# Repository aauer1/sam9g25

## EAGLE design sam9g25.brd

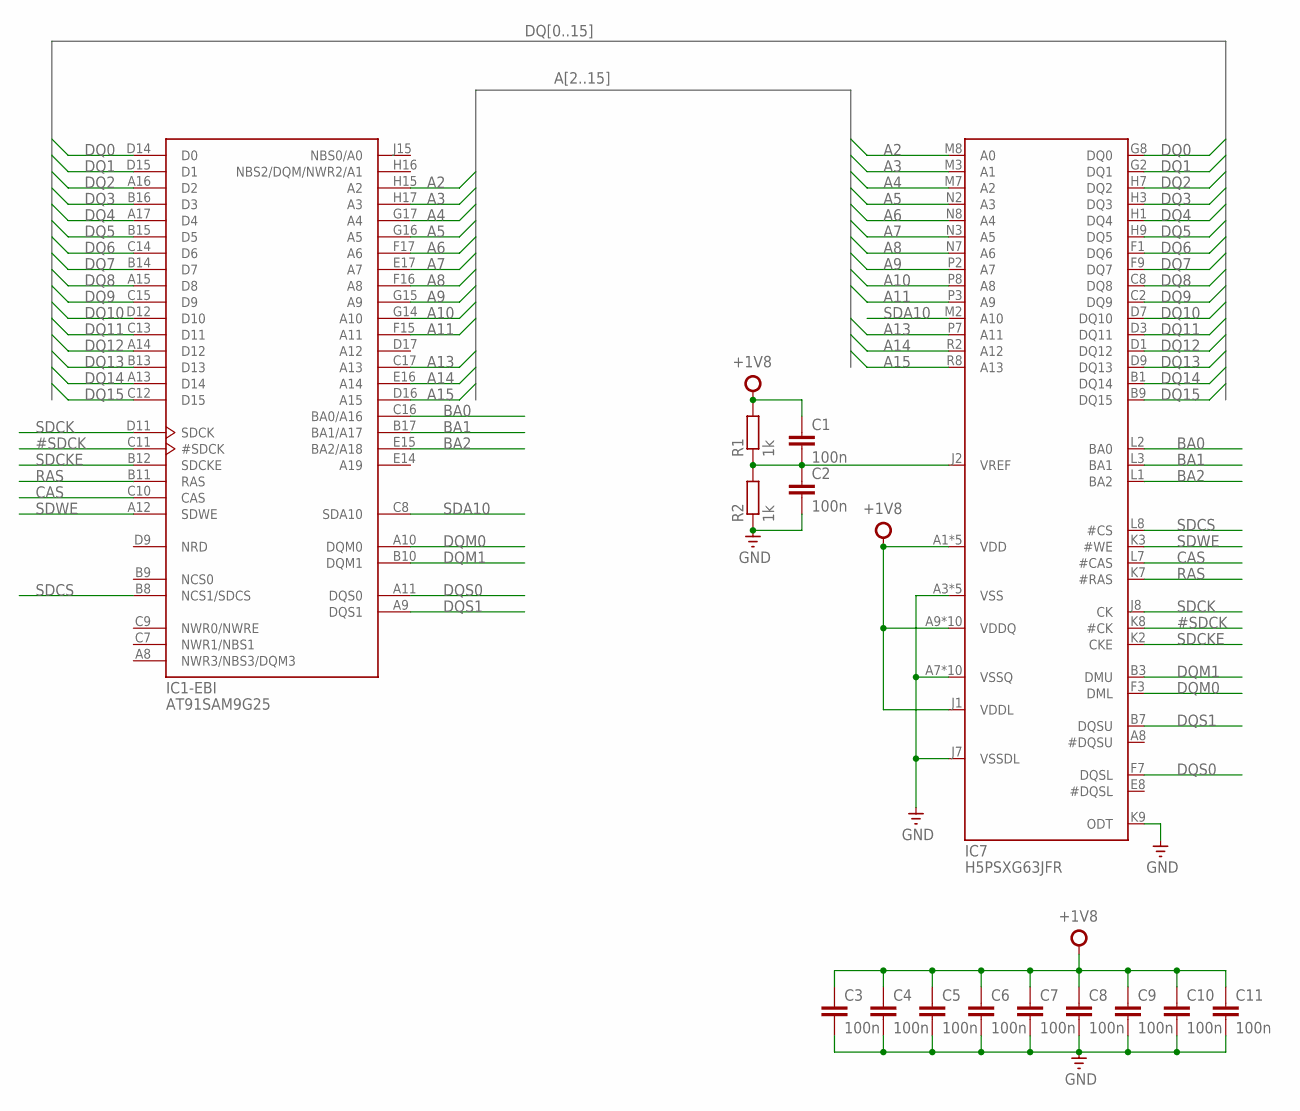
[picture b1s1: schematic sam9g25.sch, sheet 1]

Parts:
C1, C2, C3, C4, C5, C6, C7, C8, C9, C10, C11: 100n; C0603; MPN MC0603B104K250CT
IC1: AT91SAM9G25; LFBGA217; MPN AT91SAM9G25-CU
IC7: H5PSXG63JFR; FBGA84; MPN H5PS1G63JFR-S5C
R1, R2: 1k; R0603; MPN MC0063W060351K5

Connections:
#SDCK: IC1.C11 (#SDCK), IC7.K8 (#CK)
+1V8: C1.1, C3.1, C4.1, C5.1, C6.1, C7.1, C8.1, C9.1, C10.1, C11.1, IC7.A1 (VDD), IC7.A9 (VDDQ), IC7.C1 (VDDQ), IC7.C3 (VDDQ), IC7.C7 (VDDQ), IC7.C9 (VDDQ), IC7.E1 (VDD), IC7.E9 (VDDQ), IC7.G1 (VDDQ), IC7.G3 (VDDQ), IC7.G7 (VDDQ), IC7.G9 (VDDQ), IC7.J1 (VDDL), IC7.J9 (VDD), IC7.M9 (VDD), IC7.R1 (VDD), R1.2; also elsewhere on the board
A2: IC1.H15 (A2), IC7.M8 (A0)
A3: IC1.H17 (A3), IC7.M3 (A1)
A4: IC1.G17 (A4), IC7.M7 (A2)
A5: IC1.G16 (A5), IC7.N2 (A3)
A6: IC1.F17 (A6), IC7.N8 (A4)
A7: IC1.E17 (A7), IC7.N3 (A5)
A8: IC1.F16 (A8), IC7.N7 (A6)
A9: IC1.G15 (A9), IC7.P2 (A7)
A10: IC1.G14 (A10), IC7.P8 (A8)
A11: IC1.F15 (A11), IC7.P3 (A9)
A13: IC1.C17 (A13), IC7.P7 (A11)
A14: IC1.E16 (A14), IC7.R2 (A12)
A15: IC1.D16 (A15), IC7.R8 (A13)
BA0: IC1.C16 (BA0/A16), IC7.L2 (BA0)
BA1: IC1.B17 (BA1/A17), IC7.L3 (BA1)
BA2: IC1.E15 (BA2/A18), IC7.L1 (BA2)
CAS: IC1.C10 (CAS), IC7.L7 (#CAS)
DQ0: IC1.D14 (D0), IC7.G8 (DQ0)
DQ1: IC1.D15 (D1), IC7.G2 (DQ1)
DQ2: IC1.A16 (D2), IC7.H7 (DQ2)
DQ3: IC1.B16 (D3), IC7.H3 (DQ3)
DQ4: IC1.A17 (D4), IC7.H1 (DQ4)
DQ5: IC1.B15 (D5), IC7.H9 (DQ5)
DQ6: IC1.C14 (D6), IC7.F1 (DQ6)
DQ7: IC1.B14 (D7), IC7.F9 (DQ7)
DQ8: IC1.A15 (D8), IC7.C8 (DQ8)
DQ9: IC1.C15 (D9), IC7.C2 (DQ9)
DQ10: IC1.D12 (D10), IC7.D7 (DQ10)
DQ11: IC1.C13 (D11), IC7.D3 (DQ11)
DQ12: IC1.A14 (D12), IC7.D1 (DQ12)
DQ13: IC1.B13 (D13), IC7.D9 (DQ13)
DQ14: IC1.A13 (D14), IC7.B1 (DQ14)
DQ15: IC1.C12 (D15), IC7.B9 (DQ15)
DQM0: IC1.A10 (DQM0), IC7.F3 (DML)
DQM1: IC1.B10 (DQM1), IC7.B3 (DMU)
DQS0: IC1.A11 (DQS0), IC7.F7 (DQSL)
DQS1: IC1.A9 (DQS1), IC7.B7 (DQSU)
GND: C2.2, C3.2, C4.2, C5.2, C6.2, C7.2, C8.2, C9.2, C10.2, C11.2, IC7.A3 (VSS), IC7.A7 (VSSQ), IC7.B2 (VSSQ), IC7.B8 (VSSQ), IC7.D2 (VSSQ), IC7.D8 (VSSQ), IC7.E3 (VSS), IC7.E7 (VSSQ), IC7.F2 (VSSQ), IC7.F8 (VSSQ), IC7.H2 (VSSQ), IC7.H8 (VSSQ), IC7.J3 (VSS), IC7.J7 (VSSDL), IC7.K9 (ODT), IC7.N1 (VSS), IC7.P9 (VSS), R2.1; also elsewhere on the board
unnamed: C1.2, C2.1, IC7.J2 (VREF), R1.1, R2.2
RAS: IC1.B11 (RAS), IC7.K7 (#RAS)
SDA10: IC1.C8 (SDA10), IC7.M2 (A10)
SDCK: IC1.D11 (SDCK), IC7.J8 (CK)
SDCKE: IC1.B12 (SDCKE), IC7.K2 (CKE)
SDCS: IC1.B8 (NCS1/SDCS), IC7.L8 (#CS)
SDWE: IC1.A12 (SDWE), IC7.K3 (#WE)

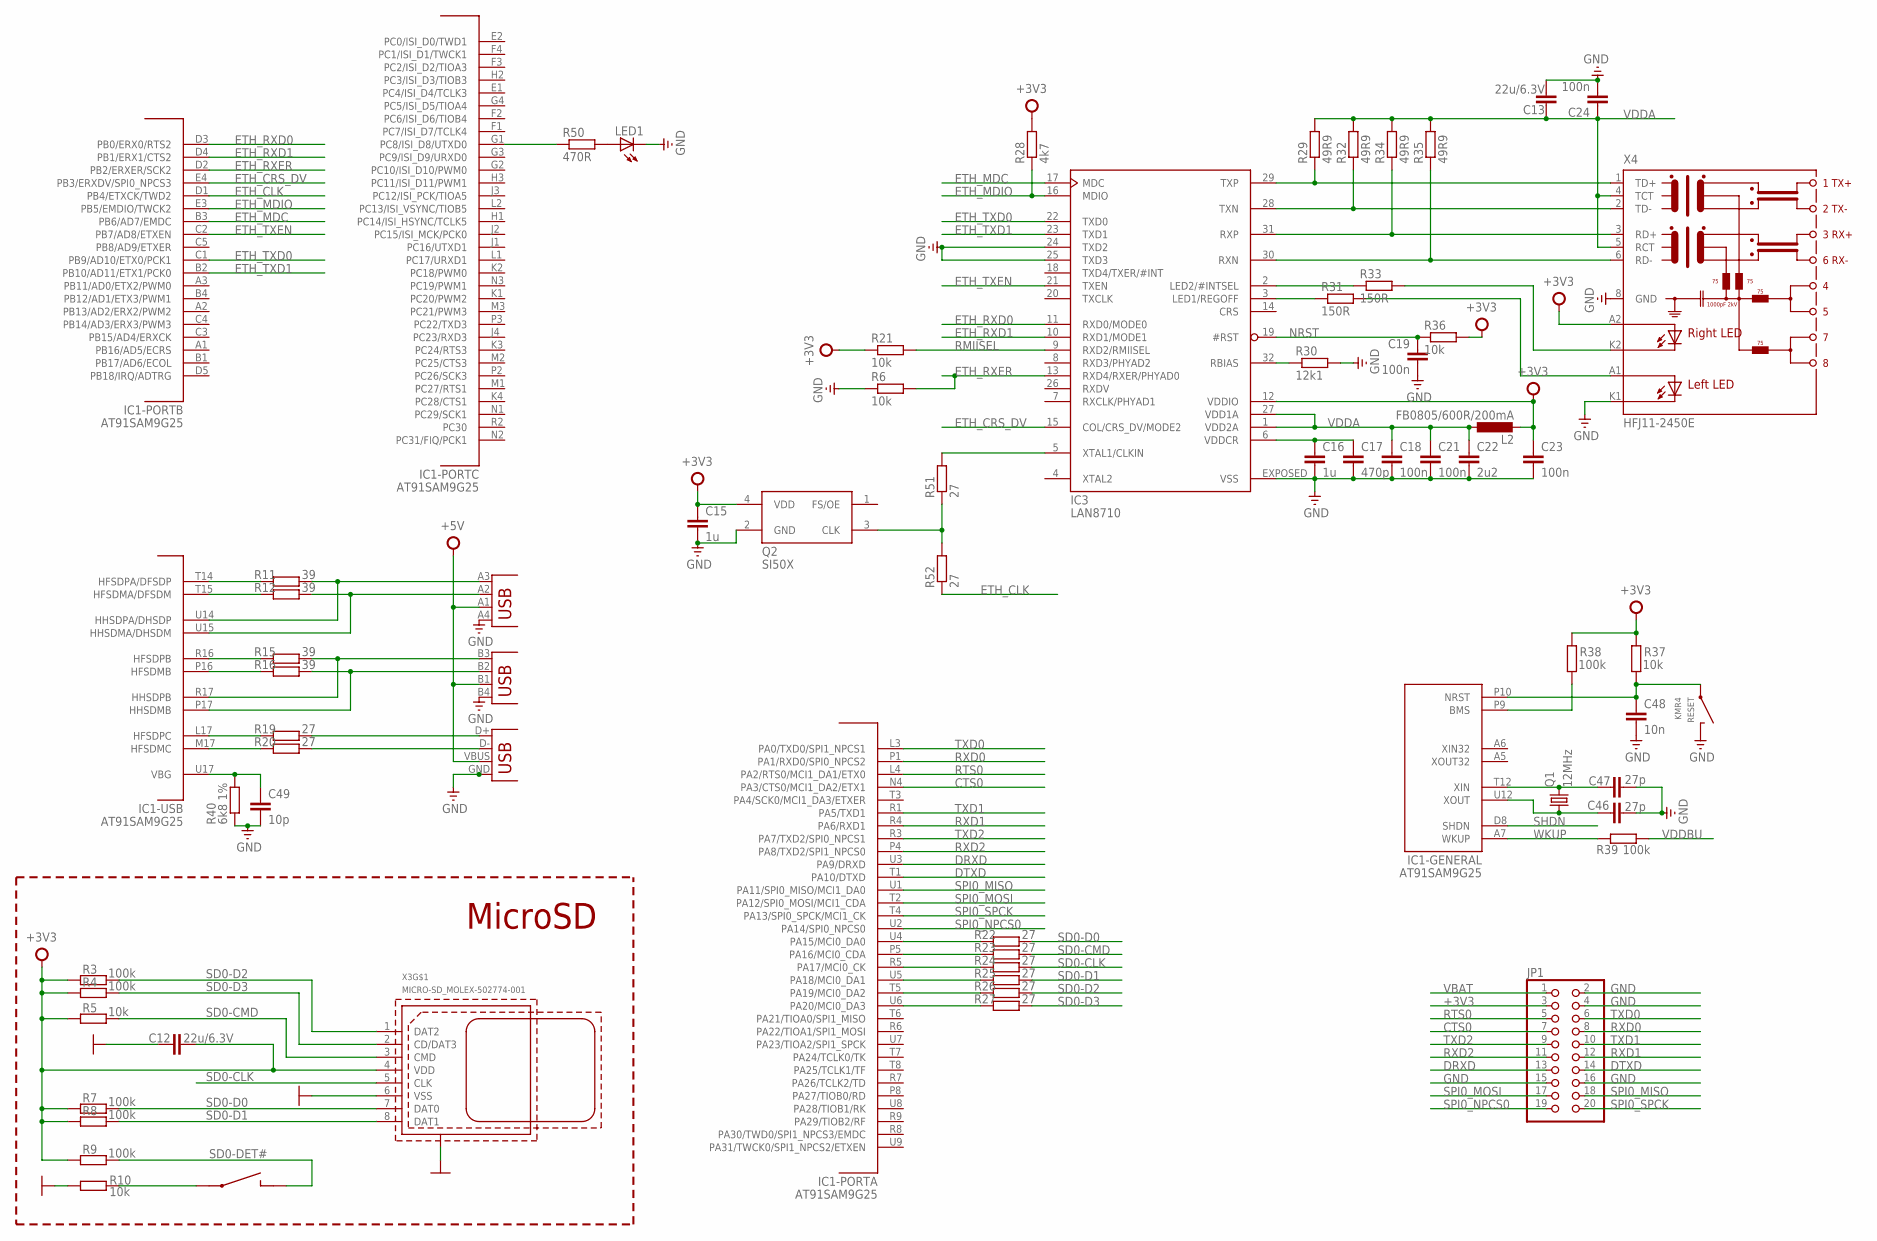
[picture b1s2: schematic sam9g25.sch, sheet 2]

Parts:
C12, C13: 22u/6.3V; C0805; MPN C2012X5R0J226M/1.25
C15: 1u; C0603; MPN MC0603N270J500CT
C16: 1u; C0603; MPN MC0603X105K100CT
C17: 470p; C0603; MPN MC0603B471K500CT
C18, C19, C21, C23, C24: 100n; C0603; MPN MC0603B104K250CT
C22: 2u2; C0603; MPN MC0603X225K6R3CT
C46, C47: 27p; C0603; MPN MC0603N270J500CT
C48: 10n; C0603; MPN MC0603B103K160CT
C49: 10p; C0603; MPN MC0603N100J500CT
IC1: AT91SAM9G25; LFBGA217; MPN AT91SAM9G25-CU
IC3: LAN8710; QFN32; MPN LAN8710A-EZK
JP1: PINHD-2X10; 2X10
L2: FB0805/600R/200mA; L2012C; MPN BLM21BD601SN1D
LED1: LEDCHIP-LED0603; CHIP-LED0603; MPN KP-1608SURCK
Q1: 12MHz; SMD5032; MPN 7A-12.000MAAJ-T
Q2: SI50X; DFN4
R3, R4, R7, R8, R9, R38, R39: 100k; R0603; MPN MC0063W06035100K
R5, R6, R10, R21, R37: 10k; R0603; MPN RC0603FR-0710KL
R11, R12, R15, R16: 39; R0603; MPN CRCW060339R0FKEA
R19, R20, R22, R23, R24, R25, R26, R27: 27; R0603; MPN MC0063W0603527R
R28: 4k7; R0603; MPN MC0063W060354K7
R29, R32, R34, R35: 49R9; R0603; MPN ERJ3GEYJ510V
R30: 12k1; R0603; MPN ERJ3EKF1212V
R31, R33: 150R; R0603; MPN MC0063W06035150R
R36: 10k; R0603; MPN ERJ3EKF1212V
R40: 6k8 1%; R0603; MPN MCMR06X6801FTL
R50: 470R; R0603; MPN MCMR06X1001FTL
R51, R52: 27; R0603; MPN RC0603FR-0710KL
RESET: KMR4; MPN KMR421NGULCLFS
X1: USB-DOUBLE; USB-DOUBLE-FCI; MPN 72309-8034BLF
X3: MICRO-SD_MOLEX-502774-001; MOLEX-MICRO-SD; MPN 502774-0891
X4: HFJ11-2450E; HFJ11_LED
X5: USB-A-HU

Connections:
+3V3: C12.2, C15.1, C23.1, IC3.12 (VDDIO), JP1.3, L2.2, Q2.4 (VDD), R3.2, R4.2, R5.2, R7.2, R8.2, R9.2, R21.1, R28.2, R36.2, R37.2, R38.2, X3.4 (VDD), X4.A2 (A-R); also elsewhere on the board
+5V: X1.A1 (VBUS), X1.B1 (VBUS), X5.VBUS; also elsewhere on the board
CTS0: IC1.N4 (PA3/CTS0/MCI1_DA2/ETX1), JP1.7
DRXD: IC1.U3 (PA9/DRXD), JP1.13
DTXD: IC1.T1 (PA10/DTXD), JP1.14
ETH_CLK: IC1.D1 (PB4/ETXCK/TWD2), R52.1
ETH_CRS_DV: IC1.E4 (PB3/ERXDV/SPI0_NPCS3), IC3.15 (COL/CRS_DV/MODE2)
ETH_MDC: IC1.B3 (PB6/AD7/EMDC), IC3.17 (MDC)
ETH_MDIO: IC1.E3 (PB5/EMDIO/TWCK2), IC3.16 (MDIO), R28.1
ETH_RXD0: IC1.D3 (PB0/ERX0/RTS2), IC3.11 (RXD0/MODE0)
ETH_RXD1: IC1.D4 (PB1/ERX1/CTS2), IC3.10 (RXD1/MODE1)
ETH_RXER: IC1.D2 (PB2/ERXER/SCK2), IC3.13 (RXD4/RXER/PHYAD0), R6.2
ETH_TXD0: IC1.C1 (PB9/AD10/ETX0/PCK1), IC3.22 (TXD0)
ETH_TXD1: IC1.B2 (PB10/AD11/ETX1/PCK0), IC3.23 (TXD1)
ETH_TXEN: IC1.C2 (PB7/AD8/ETXEN), IC3.21 (TXEN)
GND: C12.1, C13.2, C15.2, C16.2, C17.2, C18.2, C19.2, C21.2, C22.2, C23.2, C24.2, C46.2, C47.2, C48.2, C49.2, IC3.24 (TXD2), IC3.25 (TXD3), IC3.EXPOSED (VSS), JP1.2, JP1.4, JP1.15, JP1.16, LED1.C, Q2.2 (GND), R6.1, R10.2, R30.2, R40.1, RESET.2, RESET.4, X1.A4 (GND), X1.B4 (GND), X3.6 (VSS), X3.SHIELD@1, X3.SHIELD@2, X3.SHIELD@3, X3.SHIELD@4, X4.8 (GND), X4.K1 (C-L), X5.GND; also elsewhere on the board
HFSDMA: IC1.T15 (HFSDMA/DFSDM), R12.1
HFSDMB: IC1.P16 (HFSDMB), R16.1
HFSDMC: IC1.M17 (HFSDMC), R20.1
HFSDPA: IC1.T14 (HFSDPA/DFSDP), R11.1
HFSDPB: IC1.R16 (HFSDPB), R15.1
HFSDPC: IC1.L17 (HFSDPC), R19.1
HHSDMA: IC1.U15 (HHSDMA/DHSDM), R12.2, X1.A2 (D-)
HHSDMB: IC1.P17 (HHSDMB), R16.2, X1.B2 (D-)
HHSDPA: IC1.U14 (HHSDPA/DHSDP), R11.2, X1.A3 (D+)
HHSDPB: IC1.R17 (HHSDPB), R15.2, X1.B3 (D+)
unnamed: IC3.5 (XTAL1/CLKIN), R51.2
unnamed: R19.2, X5.D+
unnamed: R20.2, X5.D-
unnamed: IC1.U6 (PA20/MCI0_DA3), R27.1
unnamed: IC1.T5 (PA19/MCI0_DA2), R26.1
unnamed: IC1.U5 (PA18/MCI0_DA1), R25.1
unnamed: IC1.R5 (PA17/MCI0_CK), R24.1
unnamed: IC1.P5 (PA16/MCI0_CDA), R23.1
unnamed: IC1.U4 (PA15/MCI0_DA0), R22.1
unnamed: C49.1, IC1.U17 (VBG), R40.2
unnamed: C46.1, IC1.U12 (XOUT), Q1.1
unnamed: C47.1, IC1.T12 (XIN), Q1.2
unnamed: IC1.P9 (BMS), R38.1
unnamed: IC3.32 (RBIAS), R30.1
unnamed: C16.1, C17.1, IC3.6 (VDDCR)
unnamed: IC1.G1 (PC8/ISI_D8/UTXD0), R50.1
unnamed: LED1.A, R50.2
unnamed: Q2.3 (CLK), R51.1, R52.2
unnamed: R10.1, X3.SW1
unnamed: IC3.2 (LED2/#INTSEL), R33.1
unnamed: IC3.3 (LED1/REGOFF), R31.1
unnamed: IC3.30 (RXN), R35.1, X4.6 (RD-)
unnamed: IC3.31 (RXP), R34.1, X4.3 (RD+)
unnamed: IC3.29 (TXP), R29.1, X4.1 (TD+)
unnamed: R33.2, X4.K2 (C-R)
unnamed: R31.2, X4.A1 (A-L)
unnamed: IC3.28 (TXN), R32.1, X4.2 (TD-)
NRST: C19.1, C48.1, IC1.P10 (NRST), IC3.19 (#RST), R36.1, R37.1, RESET.1, RESET.3
RMIISEL: IC3.9 (RXD2/RMIISEL), R21.2
RTS0: IC1.L4 (PA2/RTS0/MCI1_DA1/ETX0), JP1.5
RXD0: IC1.P1 (PA1/RXD0/SPI0_NPCS2), JP1.8
RXD1: IC1.R4 (PA6/RXD1), JP1.12
RXD2: IC1.P4 (PA8/TXD2/SPI1_NPCS0), JP1.11
SD0-CLK: R24.2, X3.5 (CLK)
SD0-CMD: R5.1, R23.2, X3.3 (CMD)
SD0-D0: R7.1, R22.2, X3.7 (DAT0)
SD0-D1: R8.1, R25.2, X3.8 (DAT1)
SD0-D2: R3.1, R26.2, X3.1 (DAT2)
SD0-D3: R4.1, R27.2, X3.2 (CD/DAT3)
SD0-DET#: R9.1, X3.SW2
SHDN: IC1.D8 (SHDN)
SPI0_MISO: IC1.U1 (PA11/SPI0_MISO/MCI1_DA0), JP1.18
SPI0_MOSI: IC1.T2 (PA12/SPI0_MOSI/MCI1_CDA), JP1.17
SPI0_NPCS0: IC1.U2 (PA14/SPI0_NPCS0), JP1.19
SPI0_SPCK: IC1.T4 (PA13/SPI0_SPCK/MCI1_CK), JP1.20
TXD0: IC1.L3 (PA0/TXD0/SPI1_NPCS1), JP1.6
TXD1: IC1.R1 (PA5/TXD1), JP1.10
TXD2: IC1.R3 (PA7/TXD2/SPI0_NPCS1), JP1.9
VBAT: JP1.1; also elsewhere on the board
VDDA: C13.1, C18.1, C21.1, C22.1, C24.1, IC3.1 (VDD2A), IC3.27 (VDD1A), L2.1, R29.2, R32.2, R34.2, R35.2, X4.4 (TCT), X4.5 (RCT)
VDDBU: R39.1; also elsewhere on the board
WKUP: IC1.A7 (WKUP), R39.2

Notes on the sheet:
MicroSD

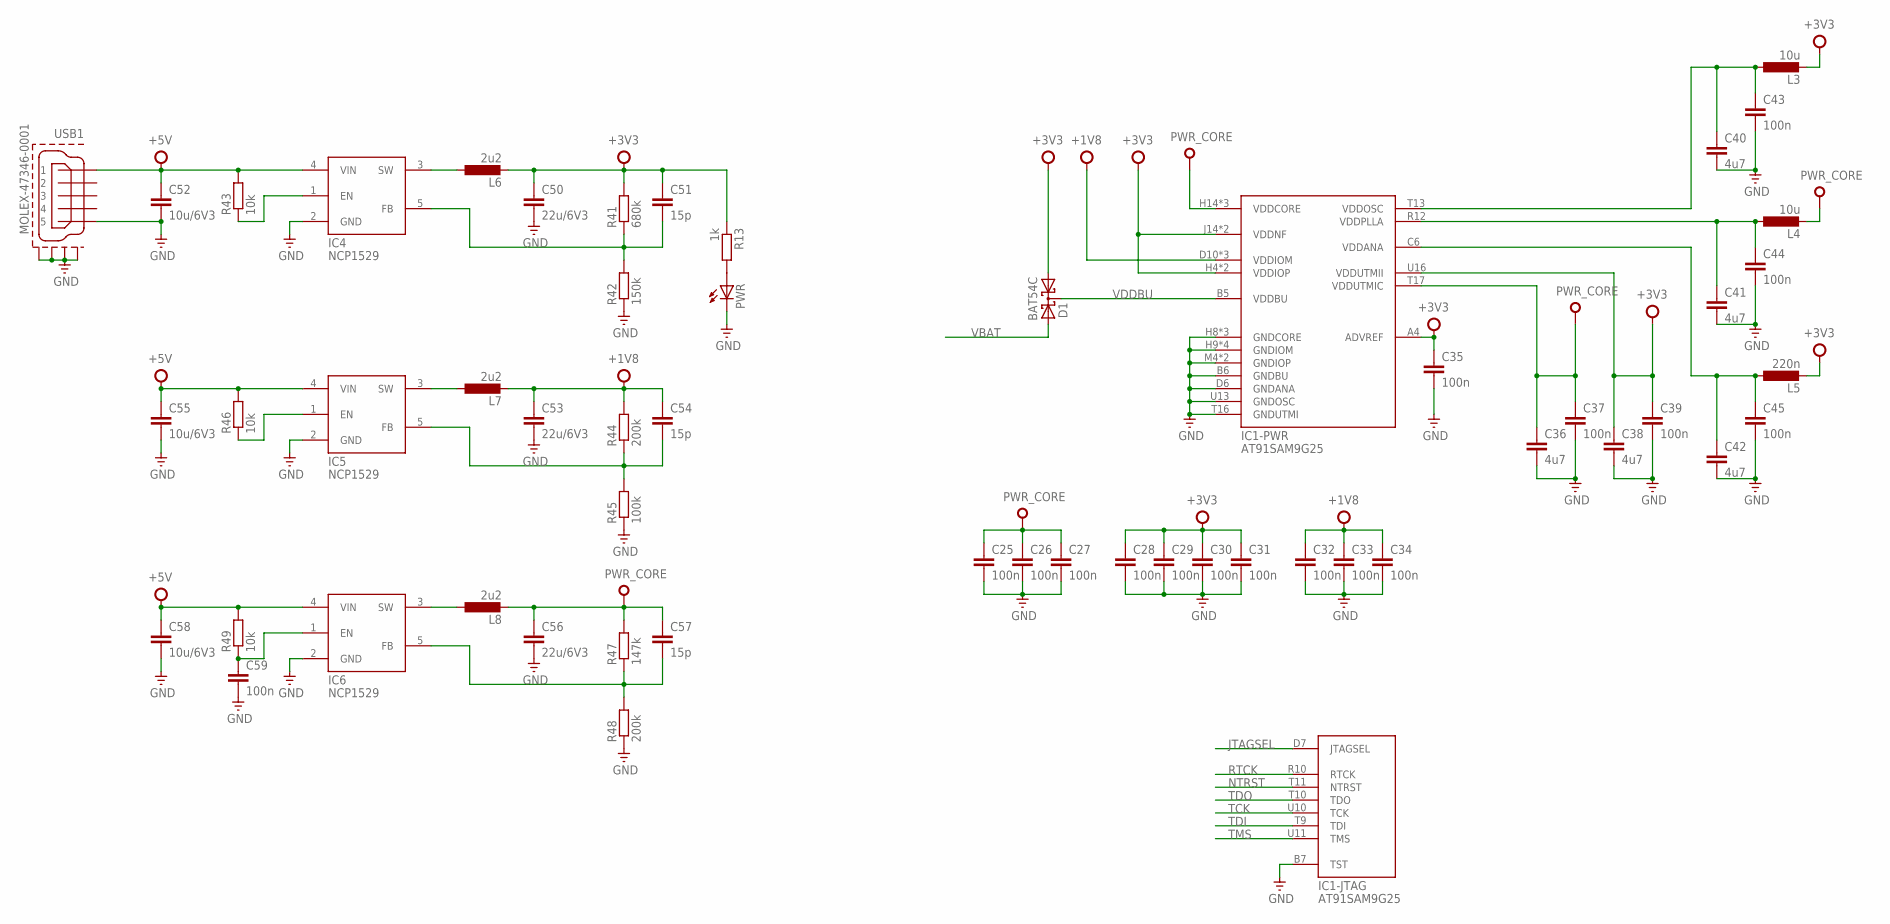
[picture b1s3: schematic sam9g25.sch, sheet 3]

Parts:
C25, C26, C27, C28, C29, C30, C31, C32, C33, C34, C35, C37, C39, C43, C44, C45, C59: 100n; C0603; MPN MC0603B104K250CT
C36, C38, C40, C41, C42: 4u7; C0603; MPN MC0603X475K6R3CT
C50, C53, C56: 22u/6V3; C0805; MPN MC0805X106K6R3CT
C51, C54, C57: 15p; C0603; MPN MC0603N150J500CT
C52, C55, C58: 10u/6V3; C0805; MPN MC0805X106K6R3CT
D1: BAT54C; SOT23; MPN BAT54C
IC1: AT91SAM9G25; LFBGA217; MPN AT91SAM9G25-CU
IC4, IC5, IC6: NCP1529; SOT23-5; MPN NCP1529ASNT1G
L3, L4: 10u; L2012C; MPN CB2012T100MR.
L5: 220n; L2012C; MPN MLZ2012DR22DT
L6, L7, L8: 2u2; L3230M; MPN ME3220-222MLB
PWR: LEDCHIP-LED0603; CHIP-LED0603; MPN KP-1608SURCK
R13: 1k; R0603; MPN MCMR06X1001FTL
R41: 680k; R0603; MPN CRCW0603680KFKEA
R42: 150k; R0603; MPN ERJ3GEYJ154V
R43, R46, R49: 10k; R0603; MPN RC0603FR-0710KL
R44, R48: 200k; R0603; MPN ERJ3EKF2003V
R45: 100k; R0603; MPN MC0063W06035100K
R47: 147k; R0603; MPN CRCW0603147KFKEA
USB1: MOLEX-47346-0001; MOLEX-47364-0001; MPN 47346-0001

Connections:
+1V8: C32.1, C33.1, C34.1, C53.1, C54.1, IC1.D10 (VDDIOM), IC1.D13 (VDDIOM), IC1.F14 (VDDIOM), L7.2, R44.2; also elsewhere on the board
+3V3: C28.1, C29.1, C30.1, C31.1, C35.1, C38.1, C39.1, C50.1, C51.1, D1.1 (A1), IC1.A4 (ADVREF), IC1.H4 (VDDIOP), IC1.J14 (VDDNF), IC1.K14 (VDDNF), IC1.P7 (VDDIOP), IC1.U16 (VDDUTMII), L3.2, L5.2, L6.2, R13.1, R41.2; also elsewhere on the board
+5V: C52.1, C55.1, C58.1, IC4.4 (VIN), IC5.4 (VIN), IC6.4 (VIN), R43.2, R46.2, R49.2, USB1.1; also elsewhere on the board
GND: C25.2, C26.2, C27.2, C28.2, C29.2, C30.2, C31.2, C32.2, C33.2, C34.2, C35.2, C36.2, C37.2, C38.2, C39.2, C40.2, C41.2, C42.2, C43.2, C44.2, C45.2, C50.2, C52.2, C53.2, C55.2, C56.2, C58.2, C59.2, IC1.B6 (GNDBU), IC1.B7 (TST), IC1.D6 (GNDANA), IC1.H8 (GNDCORE), IC1.H9 (GNDIOM), IC1.H10 (GNDIOM), IC1.J8 (GNDCORE), IC1.J9 (GNDIOM), IC1.J10 (GNDIOM), IC1.K10 (GNDCORE), IC1.M4 (GNDIOP), IC1.P6 (GNDIOP), IC1.T16 (GNDUTMI), IC1.U13 (GNDOSC), IC4.2 (GND), IC5.2 (GND), IC6.2 (GND), PWR.C, R42.1, R45.1, R48.1, USB1.5, USB1.GND1, USB1.GND2, USB1.GND3, USB1.GND4; also elsewhere on the board
JTAGSEL: IC1.D7 (JTAGSEL)
unnamed: PWR.A, R13.2
unnamed: IC4.3 (SW), L6.1
unnamed: IC5.3 (SW), L7.1
unnamed: C51.2, IC4.5 (FB), R41.1, R42.2
unnamed: C54.2, IC5.5 (FB), R44.1, R45.2
unnamed: IC4.1 (EN), R43.1
unnamed: IC5.1 (EN), R46.1
unnamed: IC6.3 (SW), L8.1
unnamed: C57.2, IC6.5 (FB), R47.1, R48.2
unnamed: C59.1, IC6.1 (EN), R49.1
NTRST: IC1.T11 (NTRST)
PWR_CORE: C25.1, C26.1, C27.1, C36.1, C37.1, C56.1, C57.1, IC1.H14 (VDDCORE), IC1.K8 (VDDCORE), IC1.K9 (VDDCORE), IC1.T17 (VDDUTMIC), L4.2, L8.2, R47.2
RTCK: IC1.R10 (RTCK)
TCK: IC1.U10 (TCK)
TDI: IC1.T9 (TDI)
TDO: IC1.T10 (TDO)
TMS: IC1.U11 (TMS)
VBAT: D1.2 (A2); also elsewhere on the board
VDDANA: C42.1, C45.1, IC1.C6 (VDDANA), L5.1
VDDBU: D1.3 (CC), IC1.B5 (VDDBU); also elsewhere on the board
VDDOSC: C40.1, C43.1, IC1.T13 (VDDOSC), L3.1
VDDPLLA: C41.1, C44.1, IC1.R12 (VDDPLLA), L4.1

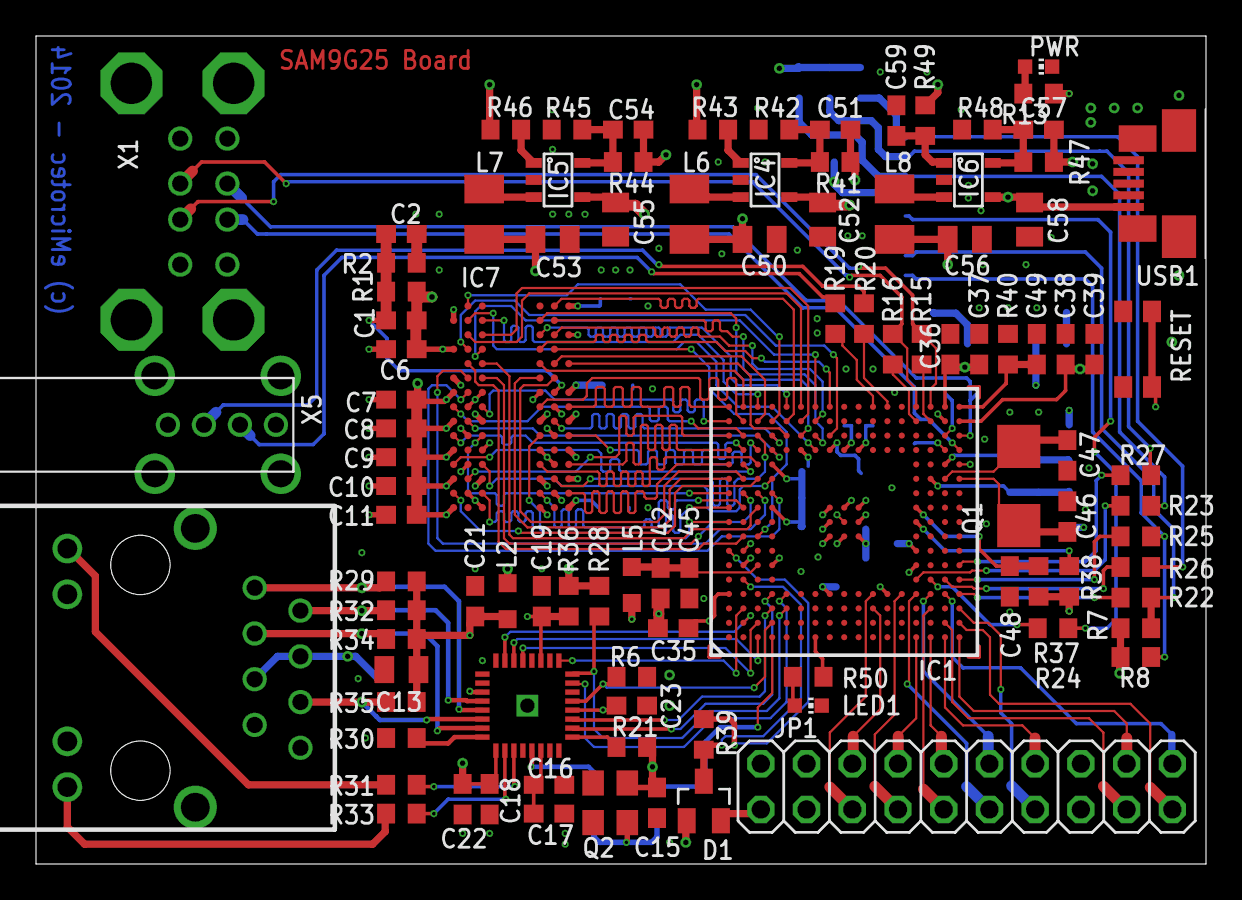
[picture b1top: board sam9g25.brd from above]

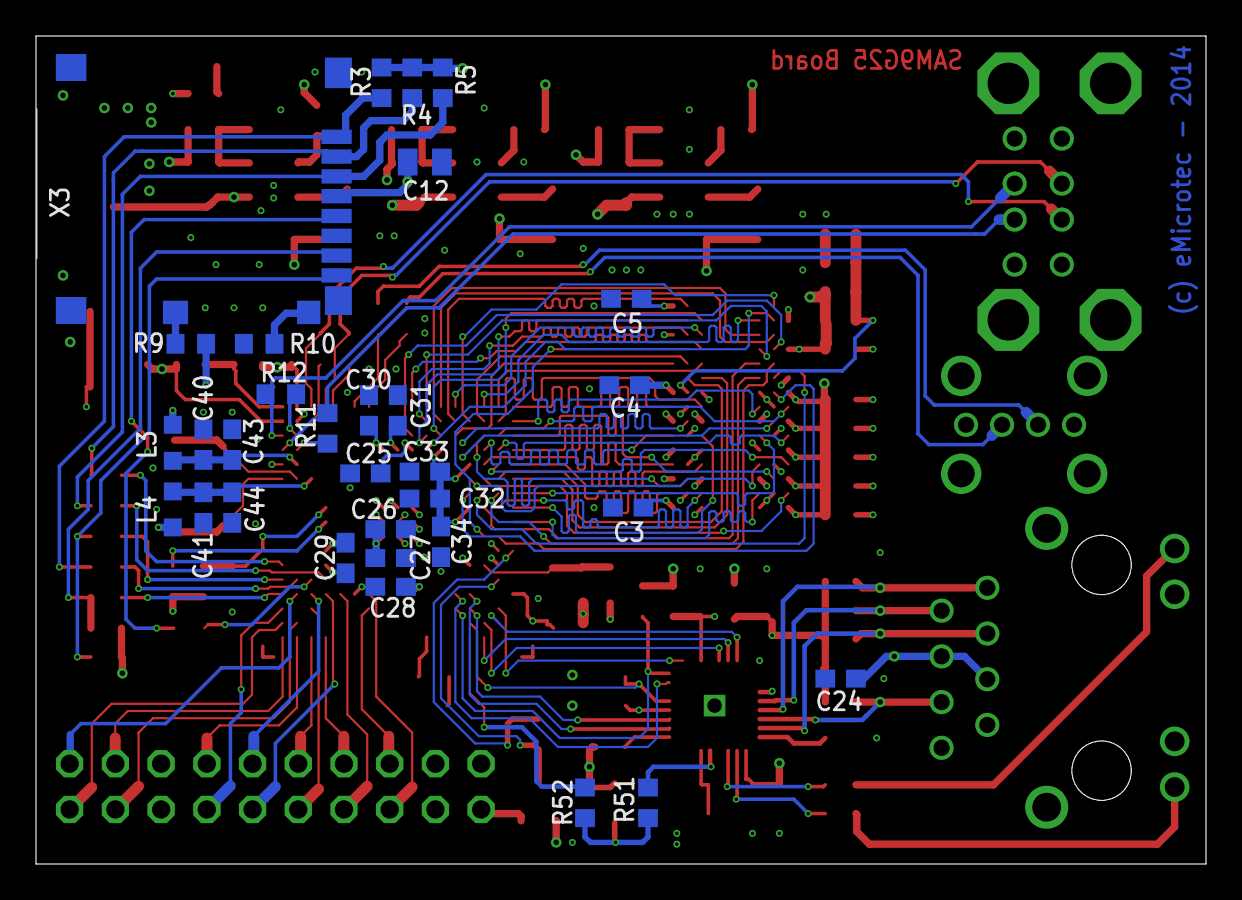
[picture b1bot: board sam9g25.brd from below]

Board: 4 copper layers, 65.0 x 46.0 mm, 131 parts (31 on the bottom side), 137 nets.

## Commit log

2014-10-15 First version, but with ethernet refclk hardware bug
2015-02-23 Fixed ethernet refclk hardware bug Fixed usb ports
2015-02-23 PDF added
2015-02-23 GNU GPL V2 licence added to schematics and board file

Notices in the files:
sam9g25.brd:
Copyright (C) 2015  Andreas Auer (aauer1@emicrotec.at)
This program is free software; you can redistribute it and/or modify
it under the terms of the GNU General Public License as published by
the Free Software Foundation; either version 2 of the License, or
(at your option) any later version.
